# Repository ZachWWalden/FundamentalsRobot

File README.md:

# FundamentalsRobot
Reference Design Robot PCB for Oklahoma Christian University's Introductory E.C.E. Course, Fundamentals.
This design is meant to guide you in designing the schematic and possibly give some general layout tips.

# Things To Note
This design is not intended to be manufactured. This was achieved using surface mount resistors, capacitors, and screw terminals that the school does not have.
Over the few lessons we will do, we will build a board that uses components the school does have and, that if you so wish could be manufactured.

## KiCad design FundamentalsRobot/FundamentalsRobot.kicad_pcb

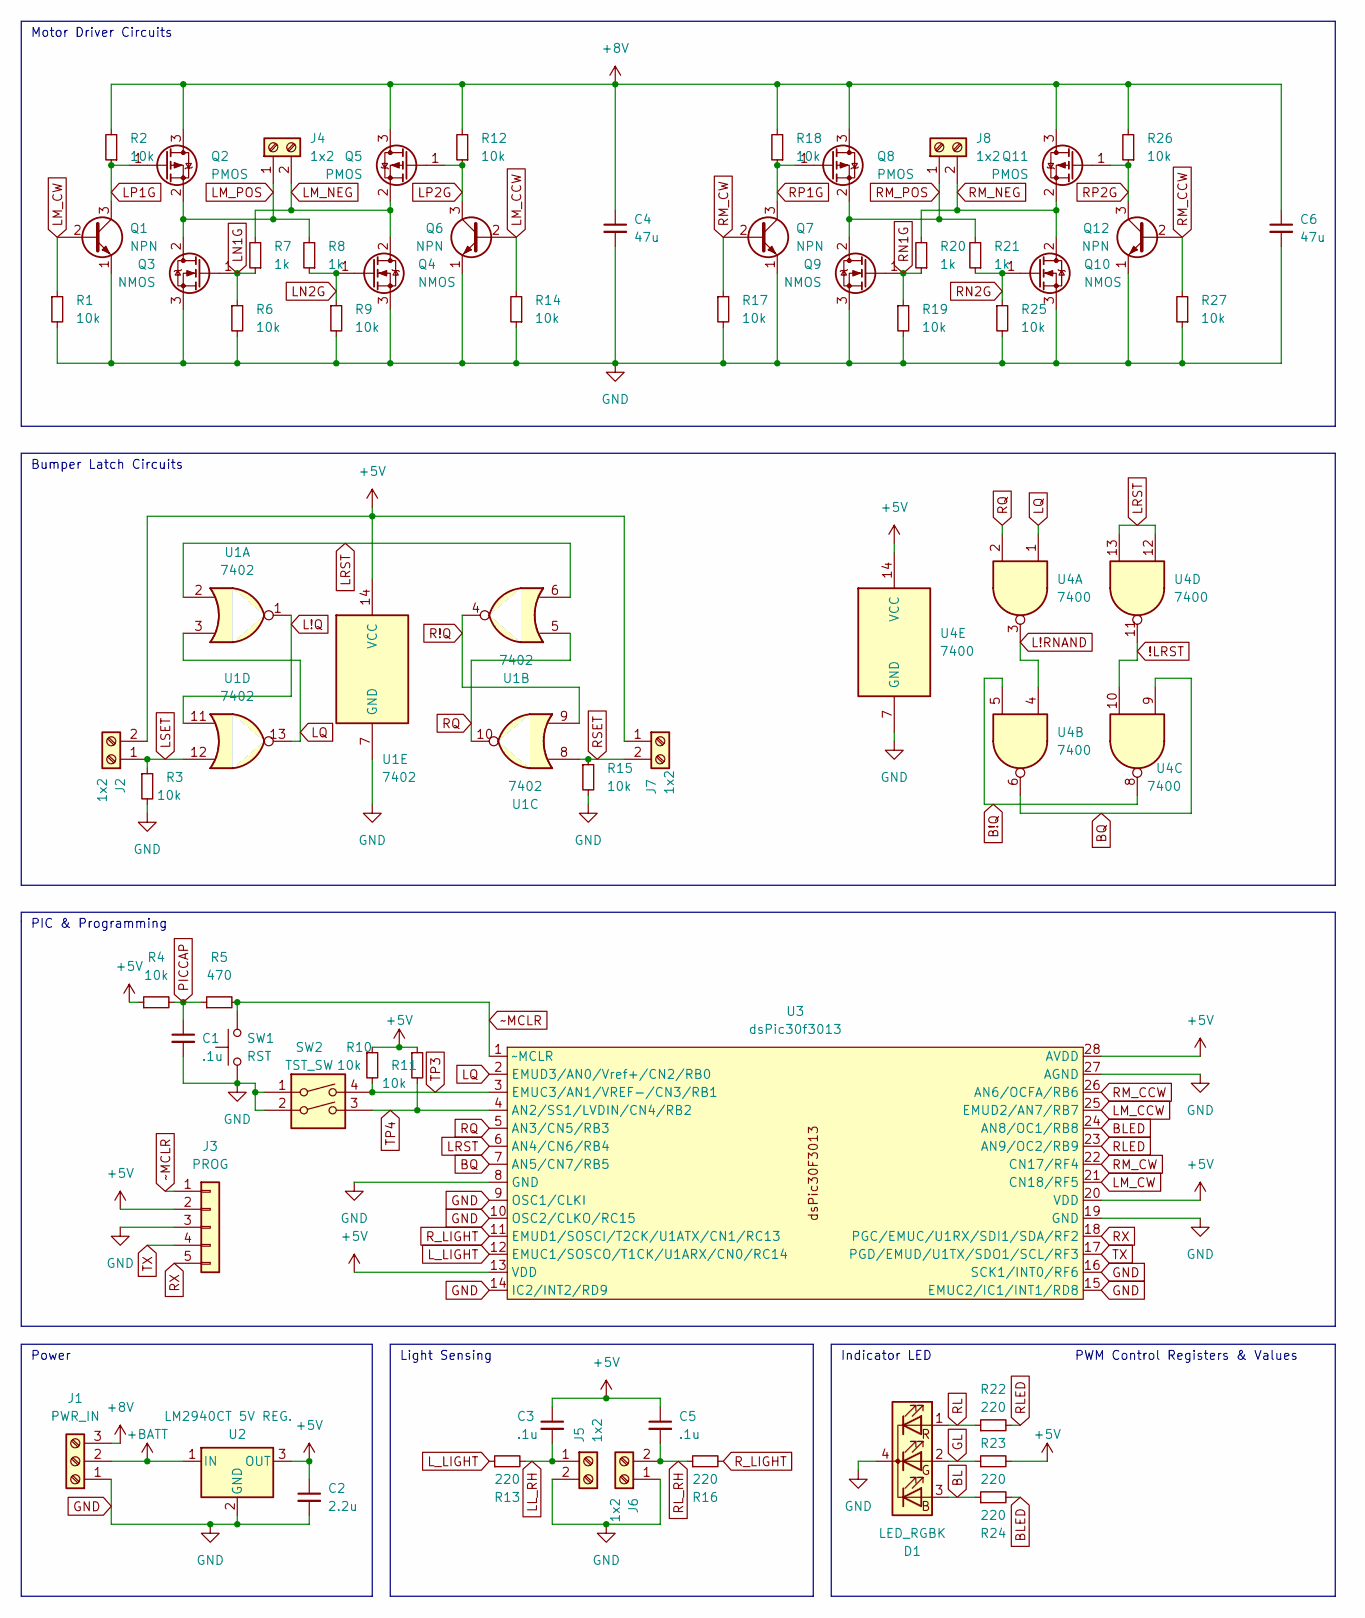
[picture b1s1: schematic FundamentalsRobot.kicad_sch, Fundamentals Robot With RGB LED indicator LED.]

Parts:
C1, C3, C5: .1u; C_0603_1608Metric
C2: 2.2u; C_0603_1608Metric
C4, C6: 47u; C_1206_3216Metric
D1: LED_RGBK; RKGB
J1: PWR_IN; TerminalBlock_Altech_AK300-3_P5.00mm
J2, J4, J5, J6, J7, J8: 1x2; TerminalBlock_Altech_AK300-2_P5.00mm
J3: PROG; PinHeader_1x05_P2.54mm_Vertical
Q1, Q6, Q7, Q12: NPN; TO-92
Q2, Q5, Q8, Q11: PMOS; TO-220-3_Vertical
Q3, Q4, Q9, Q10: NMOS; TO-220-3_Vertical
R1, R2, R3, R4, R6, R9, R10, R11, R12, R14, R15, R17, R18, R19, R25, R26, R27: 10k; R_0603_1608Metric
R5: 470; R_0603_1608Metric
R7, R8, R20, R21: 1k; R_0603_1608Metric
R13, R16, R22, R23, R24: 220; R_0603_1608Metric
SW1: RST; PinHeader_1x02_P2.54mm_Vertical
SW2: TST_SW; SW_DIP_SPSTx02_Piano_CTS_Series194-2MSTN_W7.62mm_P2.54mm
U1: 7402; DIP-14_W7.62mm
U2: LM2940CT 5V REG.; TO-220-3_Vertical
U3: dsPic30f3013; DIP-28_W7.62mm
U4: 7400; DIP-14_W7.62mm

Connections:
!LRST: U4.10, U4.11
+5V: C2.1, C3.1, C5.1, J2.2, J3.2, J7.1, R4.1, R10.1, R11.1, R23.2, U1.14 (VCC), U2.3 (OUT), U3.13 (VDD), U3.20 (VDD), U3.28 (AVDD), U4.14 (VCC)
+8V: C4.1, C6.1, J1.3, Q2.3 (D), Q5.3 (D), Q8.3 (D), Q11.3 (D), R2.2, R12.2, R18.2, R26.2
+BATT: J1.2, U2.1 (IN)
B!Q: U4.5, U4.8
BL: D1.3 (BA), R24.1
BLED: R24.2, U3.24 (AN8/OC1/RB8)
BQ: U3.7 (AN5/CN7/RB5), U4.6, U4.9
GL: D1.2 (GA), R23.1
GND: C1.2, C2.2, C4.2, C6.2, D1.4 (K), J1.1, J3.3, J5.2, J6.1, Q1.1 (E), Q3.3 (S), Q4.3 (S), Q6.1 (E), Q7.1 (E), Q9.3 (S), Q10.3 (S), Q12.1 (E), R1.2, R3.2, R6.2, R9.2, R14.1, R15.2, R17.2, R19.2, R25.2, R27.1, SW1.1, SW2.1, SW2.2, U1.7 (GND), U2.2 (GND), U3.8 (GND), U3.9 (OSC1/CLKI), U3.10 (OSC2/CLKO/RC15), U3.14 (IC2/INT2/RD9), U3.15 (EMUC2/IC1/INT1/RD8), U3.16 (SCK1/INT0/RF6), U3.19 (GND), U3.27 (AGND), U4.7 (GND)
L!Q: U1.1, U1.11
L!RNAND: U4.3, U4.4
LL_RH: C3.2, J5.1, R13.2
LM_CCW: Q6.2 (B), R14.2, U3.25 (EMUD2/AN7/RB7)
LM_CW: Q1.2 (B), R1.1, U3.21 (CN18/RF5)
LM_NEG: J4.2, Q4.2 (D), Q5.2 (S), R7.2
LM_POS: J4.1, Q2.2 (S), Q3.2 (D), R8.2
LN1G: Q3.1 (G), R6.1, R7.1
LN2G: Q4.1 (G), R8.1, R9.1
LP1G: Q1.3 (C), Q2.1 (G), R2.1
LP2G: Q5.1 (G), Q6.3 (C), R12.1
LQ: U1.3, U1.13, U3.2 (EMUD3/AN0/Vref+/CN2/RB0), U4.1
LRST: U1.2, U1.6, U3.6 (AN4/CN6/RB4), U4.12, U4.13
LSET: J2.1, R3.1, U1.12
L_LIGHT: R13.1, U3.12 (EMUC1/SOSCO/T1CK/U1ARX/CN0/RC14)
PICCAP: C1.1, R4.2, R5.1
R!Q: U1.4, U1.9
RL: D1.1 (RA), R22.1
RLED: R22.2, U3.23 (AN9/OC2/RB9)
RL_RH: C5.2, J6.2, R16.1
RM_CCW: Q12.2 (B), R27.2, U3.26 (AN6/OCFA/RB6)
RM_CW: Q7.2 (B), R17.1, U3.22 (CN17/RF4)
RM_NEG: J8.2, Q10.2 (D), Q11.2 (S), R20.2
RM_POS: J8.1, Q8.2 (S), Q9.2 (D), R21.2
RN1G: Q9.1 (G), R19.1, R20.1
RN2G: Q10.1 (G), R21.1, R25.1
RP1G: Q7.3 (C), Q8.1 (G), R18.1
RP2G: Q11.1 (G), Q12.3 (C), R26.1
RQ: U1.5, U1.10, U3.5 (AN3/CN5/RB3), U4.2
RSET: J7.2, R15.1, U1.8
RX: J3.5, U3.18 (PGC/EMUC/U1RX/SDI1/SDA/RF2)
R_LIGHT: R16.2, U3.11 (EMUD1/SOSCI/T2CK/U1ATX/CN1/RC13)
TP3: R10.2, SW2.4, U3.3 (EMUC3/AN1/VREF-/CN3/RB1)
TP4: R11.2, SW2.3, U3.4 (AN2/SS1/LVDIN/CN4/RB2)
TX: J3.4, U3.17 (PGD/EMUD/U1TX/SDO1/SCL/RF3)
~MCLR: J3.1, R5.2, SW1.2, U3.1 (~MCLR)

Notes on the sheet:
Indicator LED
Power
Motor Driver Circuits
Light Sensing
PIC & Programming
Bumper Latch Circuits
PWM Control Registers & Values

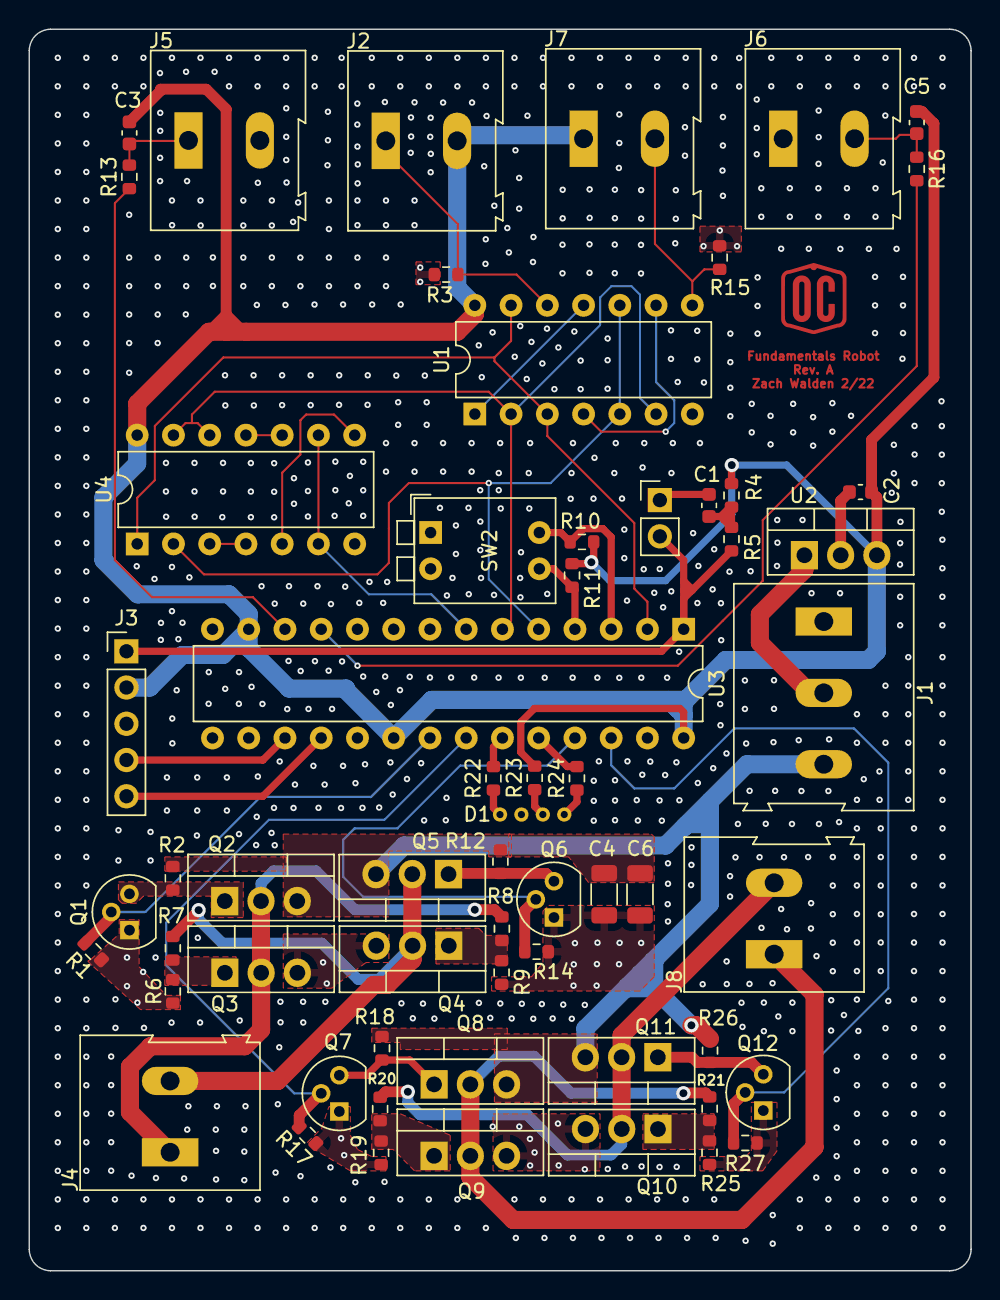
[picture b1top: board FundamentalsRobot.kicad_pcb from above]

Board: 4 copper layers, 66.0 x 87.0 mm, 60 parts (0 on the bottom side), 46 nets.

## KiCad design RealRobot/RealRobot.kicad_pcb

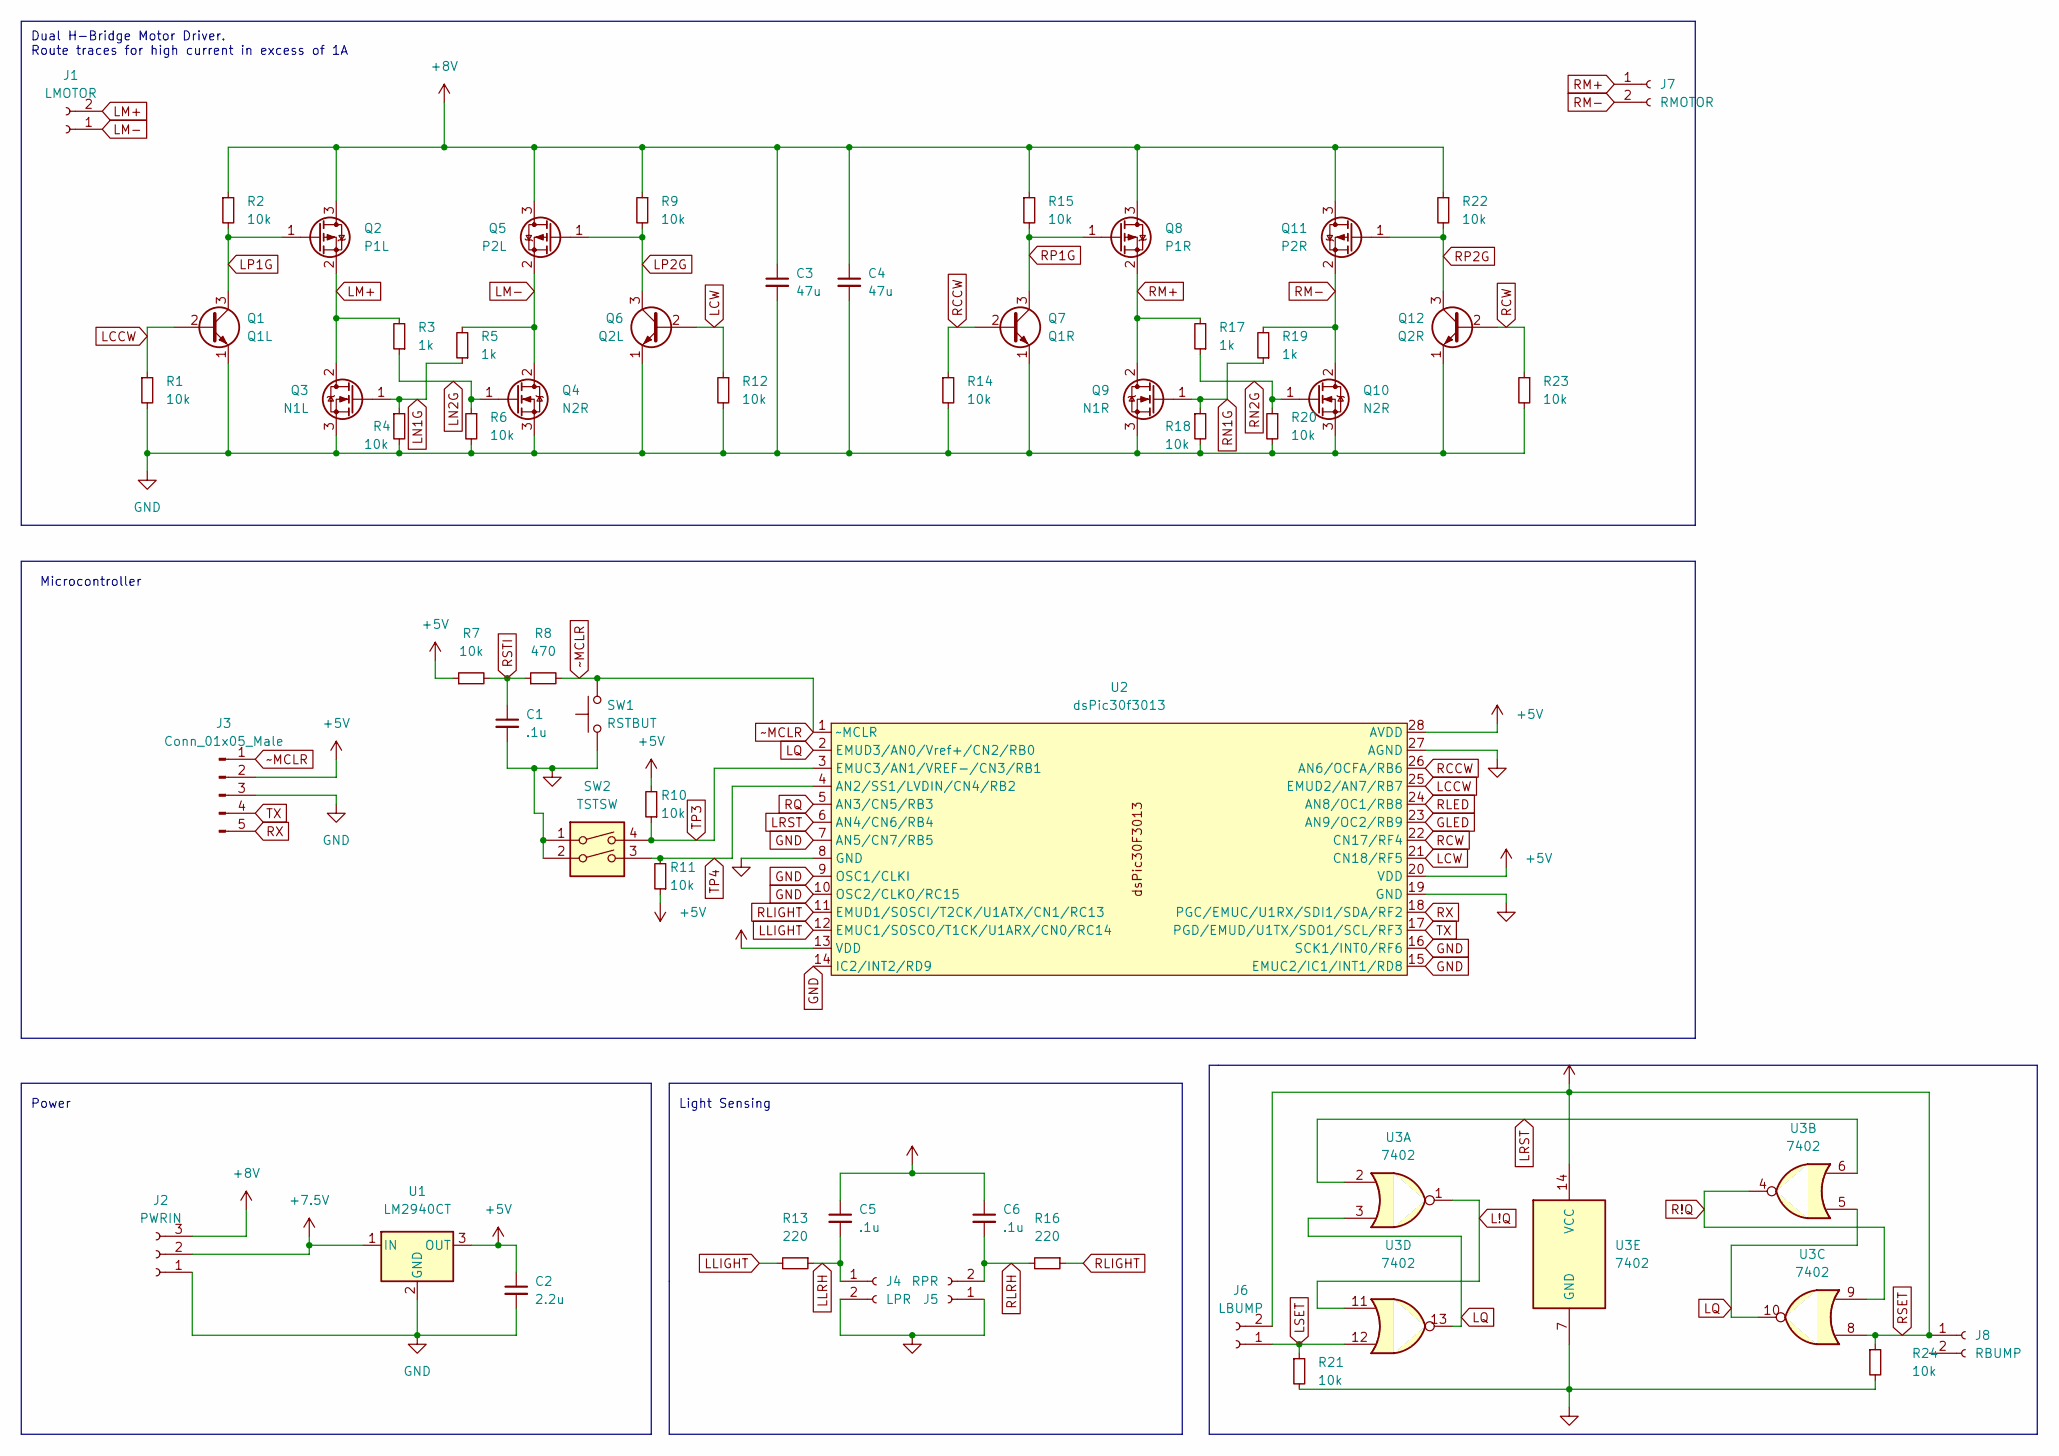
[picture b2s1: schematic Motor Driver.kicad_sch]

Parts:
C1, C5, C6: .1u; CP_Radial_D4.0mm_P1.50mm
C2: 2.2u; CP_Radial_D5.0mm_P2.00mm
C3, C4: 47u; CP_Radial_D5.0mm_P2.50mm
J1: LMOTOR
J2: PWRIN; PinHeader_1x03_P2.54mm_Vertical
J3: Conn_01x05_Male; PinHeader_1x05_P2.54mm_Vertical
J4: LPR; PinHeader_1x02_P2.54mm_Vertical
J5: RPR; PinHeader_1x02_P2.54mm_Vertical
J6: LBUMP; PinHeader_1x02_P2.54mm_Vertical
J7: RMOTOR; PinHeader_1x02_P2.54mm_Vertical
J8: RBUMP; PinHeader_1x02_P2.54mm_Vertical
Q1: Q1L; TO-92
Q2: P1L; TO-220-3_Vertical
Q3: N1L; TO-220-3_Vertical
Q4, Q10: N2R; TO-220-3_Vertical
Q5: P2L; TO-220-3_Vertical
Q6: Q2L; TO-92
Q7: Q1R; TO-92
Q8: P1R; TO-220-3_Vertical
Q9: N1R; TO-220-3_Vertical
Q11: P2R; TO-220-3_Vertical
Q12: Q2R; TO-92
R1, R2, R4, R6, R7, R9, R10, R11, R12, R14, R15, R18, R20, R21, R22, R23, R24: 10k; R_Axial_DIN0207_L6.3mm_D2.5mm_P10.16mm_Horizontal
R3, R5, R17, R19: 1k; R_Axial_DIN0207_L6.3mm_D2.5mm_P10.16mm_Horizontal
R8: 470; R_Axial_DIN0207_L6.3mm_D2.5mm_P10.16mm_Horizontal
R13, R16: 220; R_Axial_DIN0207_L6.3mm_D2.5mm_P10.16mm_Horizontal
SW1: RSTBUT; PinHeader_1x02_P2.54mm_Vertical
SW2: TSTSW; SW_DIP_SPSTx02_Piano_CTS_Series194-2MSTN_W7.62mm_P2.54mm
U1: LM2940CT; TO-220-3_Vertical
U2: dsPic30f3013; DIP-28_W7.62mm
U3: 7402; DIP-14_W7.62mm

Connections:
+7.5V: J2.2, U1.1 (IN)
+8V: C3.1, C4.1, J2.3, Q2.3 (D), Q5.3 (D), Q8.3 (D), Q11.3 (D), R2.1, R9.1, R15.1, R22.1
GLED: U2.23 (AN9/OC2/RB9)
L!Q: U3.1, U3.11
LCCW: Q1.2 (B), R1.1, U2.25 (EMUD2/AN7/RB7)
LCW: Q6.2 (B), R12.1, U2.21 (CN18/RF5)
LLIGHT: R13.2, U2.12 (EMUC1/SOSCO/T1CK/U1ARX/CN0/RC14)
LLRH: C5.2, J4.1, R13.1
LM+: J1.2, Q2.2 (S), Q3.2 (D), R3.2
LM-: J1.1, Q4.2 (D), Q5.2 (S), R5.2
LN1G: Q3.1 (G), R4.1, R5.1
LN2G: Q4.1 (G), R3.1, R6.1
LP1G: Q1.3 (C), Q2.1 (G), R2.2
LP2G: Q5.1 (G), Q6.3 (C), R9.2
LQ: U2.2 (EMUD3/AN0/Vref+/CN2/RB0), U3.3, U3.5, U3.10, U3.13
LRST: U2.6 (AN4/CN6/RB4), U3.2, U3.6
LSET: J6.1, R21.1, U3.12
R!Q: U3.4, U3.9
RCCW: Q7.2 (B), R14.1, U2.26 (AN6/OCFA/RB6)
RCW: Q12.2 (B), R23.1, U2.22 (CN17/RF4)
RLED: U2.24 (AN8/OC1/RB8)
RLIGHT: R16.1, U2.11 (EMUD1/SOSCI/T2CK/U1ATX/CN1/RC13)
RLRH: C6.2, J5.2, R16.2
RM+: J7.1, Q8.2 (S), Q9.2 (D), R17.2
RM-: J7.2, Q10.2 (D), Q11.2 (S), R19.2
RN1G: Q9.1 (G), R18.1, R19.1
RN2G: Q10.1 (G), R17.1, R20.1
RP1G: Q7.3 (C), Q8.1 (G), R15.2
RP2G: Q11.1 (G), Q12.3 (C), R22.2
RQ: U2.5 (AN3/CN5/RB3)
RSTI: C1.1, R7.2, R8.1
RX: J3.5, U2.18 (PGC/EMUC/U1RX/SDI1/SDA/RF2)
TP3: R10.1, SW2.4, U2.3 (EMUC3/AN1/VREF-/CN3/RB1)
TP4: R11.2, SW2.3, U2.4 (AN2/SS1/LVDIN/CN4/RB2)
TX: J3.4, U2.17 (PGD/EMUD/U1TX/SDO1/SCL/RF3)
~MCLR: J3.1, R8.2, SW1.2, U2.1 (~MCLR)

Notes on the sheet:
Microcontroller
Light Sensing
Dual H-Bridge Motor Driver. Route traces for high current in excess of 1A
Power

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
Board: 2 copper layers, 55 parts (0 on the bottom side), 35 nets, no tracks yet.

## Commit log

2022-03-08 Fixed Bumper Switch Pull Up Issue
2022-03-08 fix readme issue
2022-03-29 Added Schematic Done @ meeting along with a few clean ups.
2022-04-28 Final Real Robot Controller Board
